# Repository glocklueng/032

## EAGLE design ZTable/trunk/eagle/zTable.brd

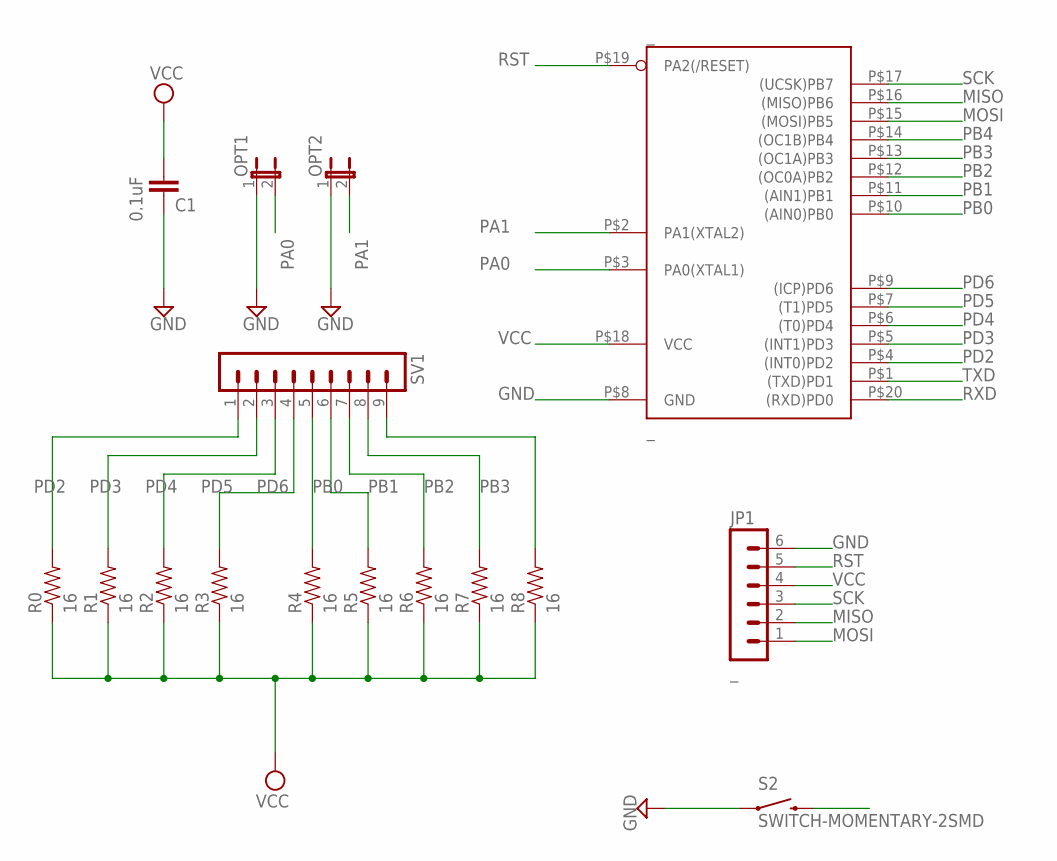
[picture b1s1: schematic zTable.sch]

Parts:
C1: 0.1uF; 0805
JP1: _; MA06-1
OPT1, OPT2: JUMPER-2PTH; 1X02
R0, R1, R2, R3, R4, R5, R6, R7, R8: 16; 0805
S2: SWITCH-MOMENTARY-2SMD; TACTILE_SWITCH_SMD
SV1: MA09-1
_: _; MLF20

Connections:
GND: C1.2, JP1.6, OPT1.1, OPT2.1, S2.1, _.P$8 (GND)
MISO: JP1.2, _.P$16 ((MISO)PB6)
MOSI: JP1.1, _.P$15 ((MOSI)PB5)
PA0: OPT1.2, _.P$3 (PA0(XTAL1))
PA1: OPT2.2, _.P$2 (PA1(XTAL2))
PB0: R5.2, SV1.6, _.P$10 ((AIN0)PB0)
PB1: R6.2, SV1.7, _.P$11 ((AIN1)PB1)
PB2: R7.2, SV1.8, _.P$12 ((OC0A)PB2)
PB3: R8.2, SV1.9, _.P$13 ((OC1A)PB3)
PB4: S2.3 (2), _.P$14 ((OC1B)PB4)
PD2: R0.2, SV1.1, _.P$4 ((INT0)PD2)
PD3: R1.2, SV1.2, _.P$5 ((INT1)PD3)
PD4: R2.2, SV1.3, _.P$6 ((T0)PD4)
PD5: R3.2, SV1.4, _.P$7 ((T1)PD5)
PD6: R4.2, SV1.5, _.P$9 ((ICP)PD6)
RST: JP1.5, _.P$19 (PA2(/RESET))
RXD: _.P$20 ((RXD)PD0)
SCK: JP1.3, _.P$17 ((UCSK)PB7)
TXD: _.P$1 ((TXD)PD1)
VCC: C1.1, JP1.4, R0.1, R1.1, R2.1, R3.1, R4.1, R5.1, R6.1, R7.1, R8.1, _.P$18 (VCC)

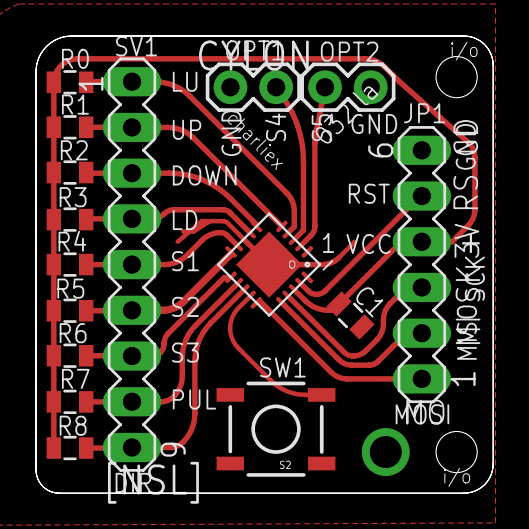
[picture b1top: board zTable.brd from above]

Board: 2 copper layers, 25.4 x 25.4 mm, 16 parts (0 on the bottom side), 18 nets.
